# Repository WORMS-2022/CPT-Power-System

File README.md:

# CPT-Power-System
 Power sharing architecture and supporting electronics

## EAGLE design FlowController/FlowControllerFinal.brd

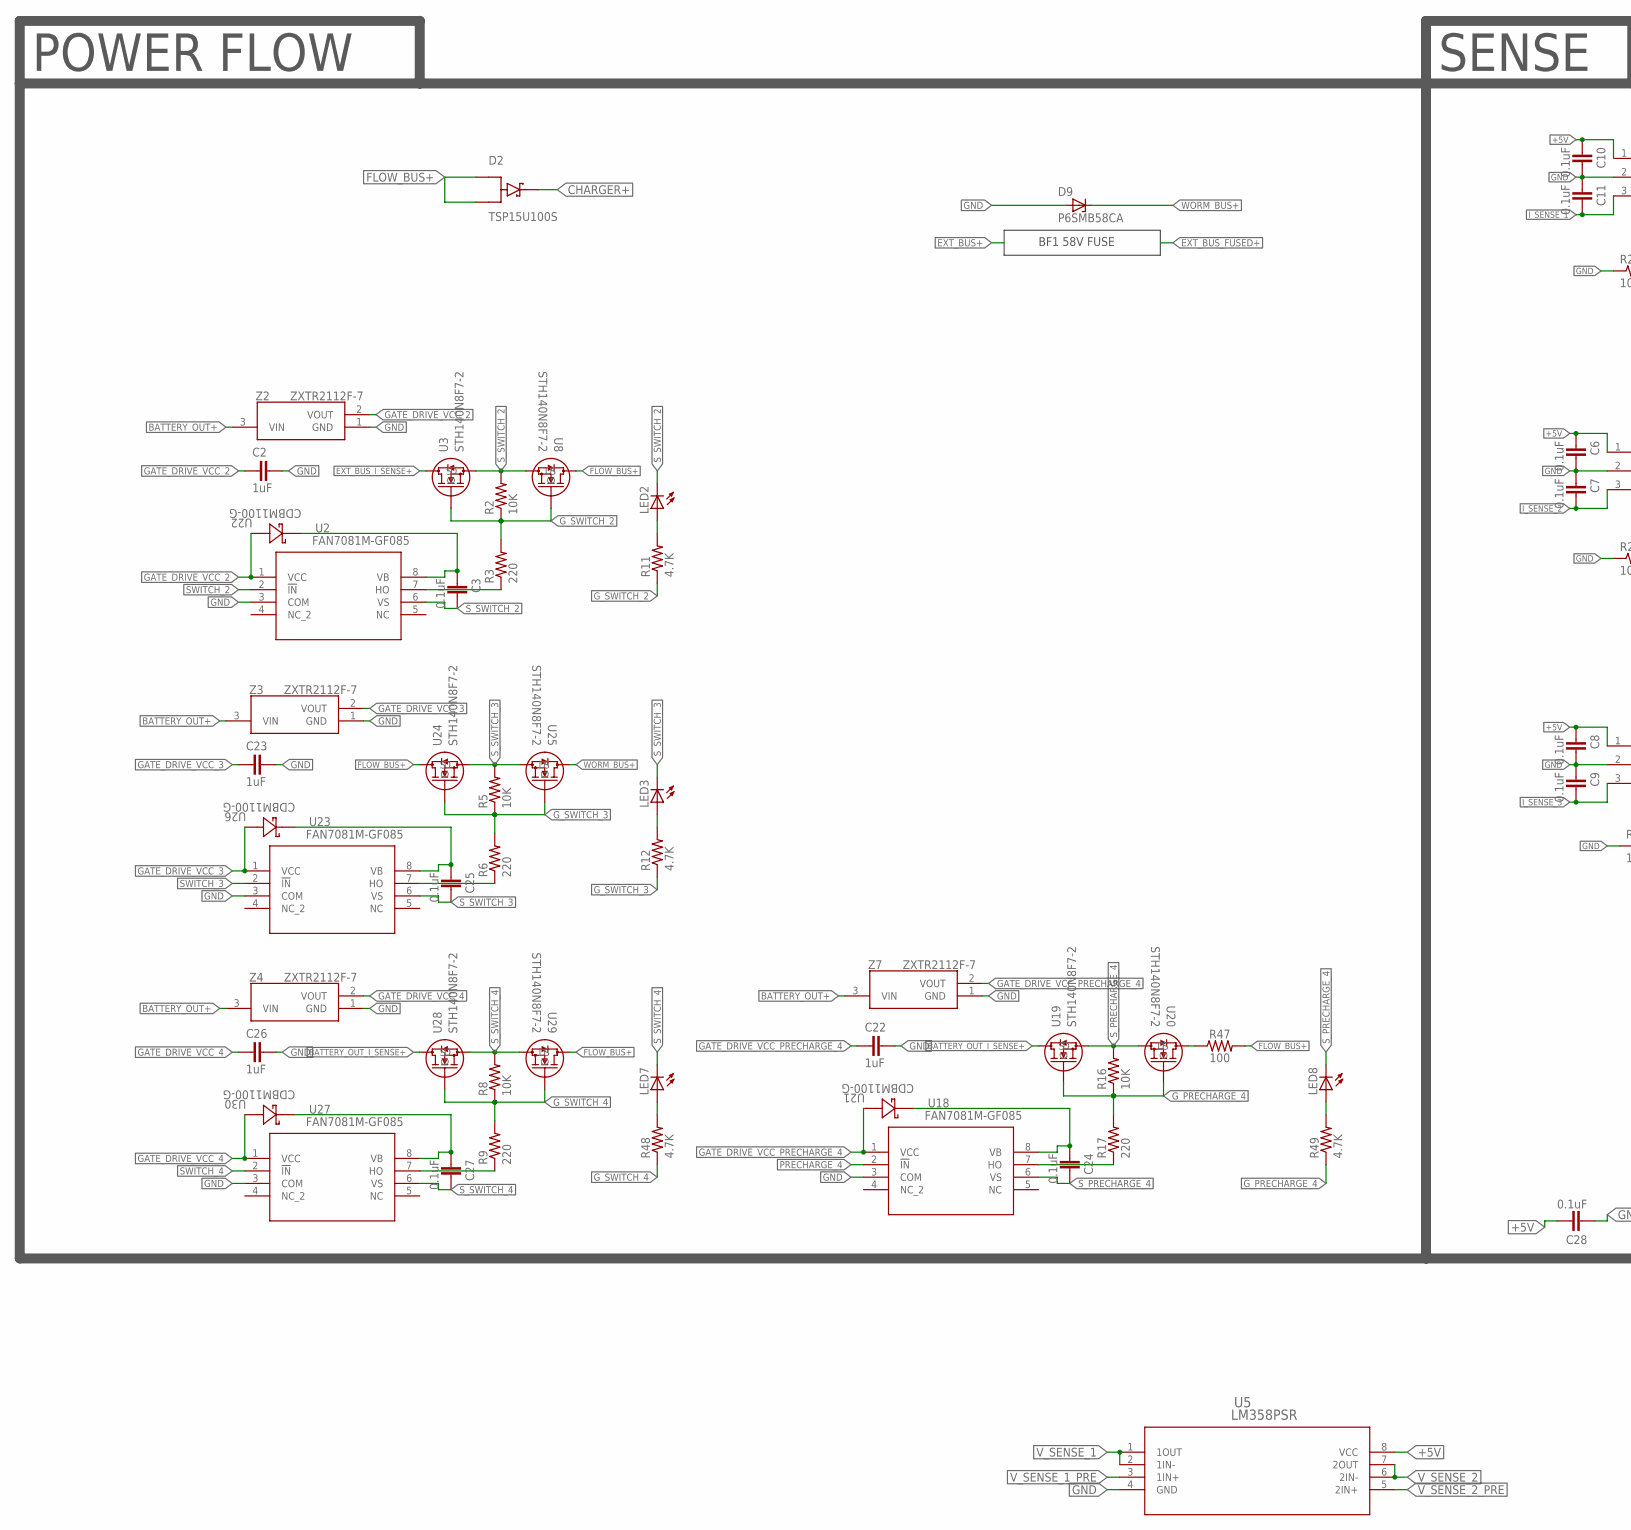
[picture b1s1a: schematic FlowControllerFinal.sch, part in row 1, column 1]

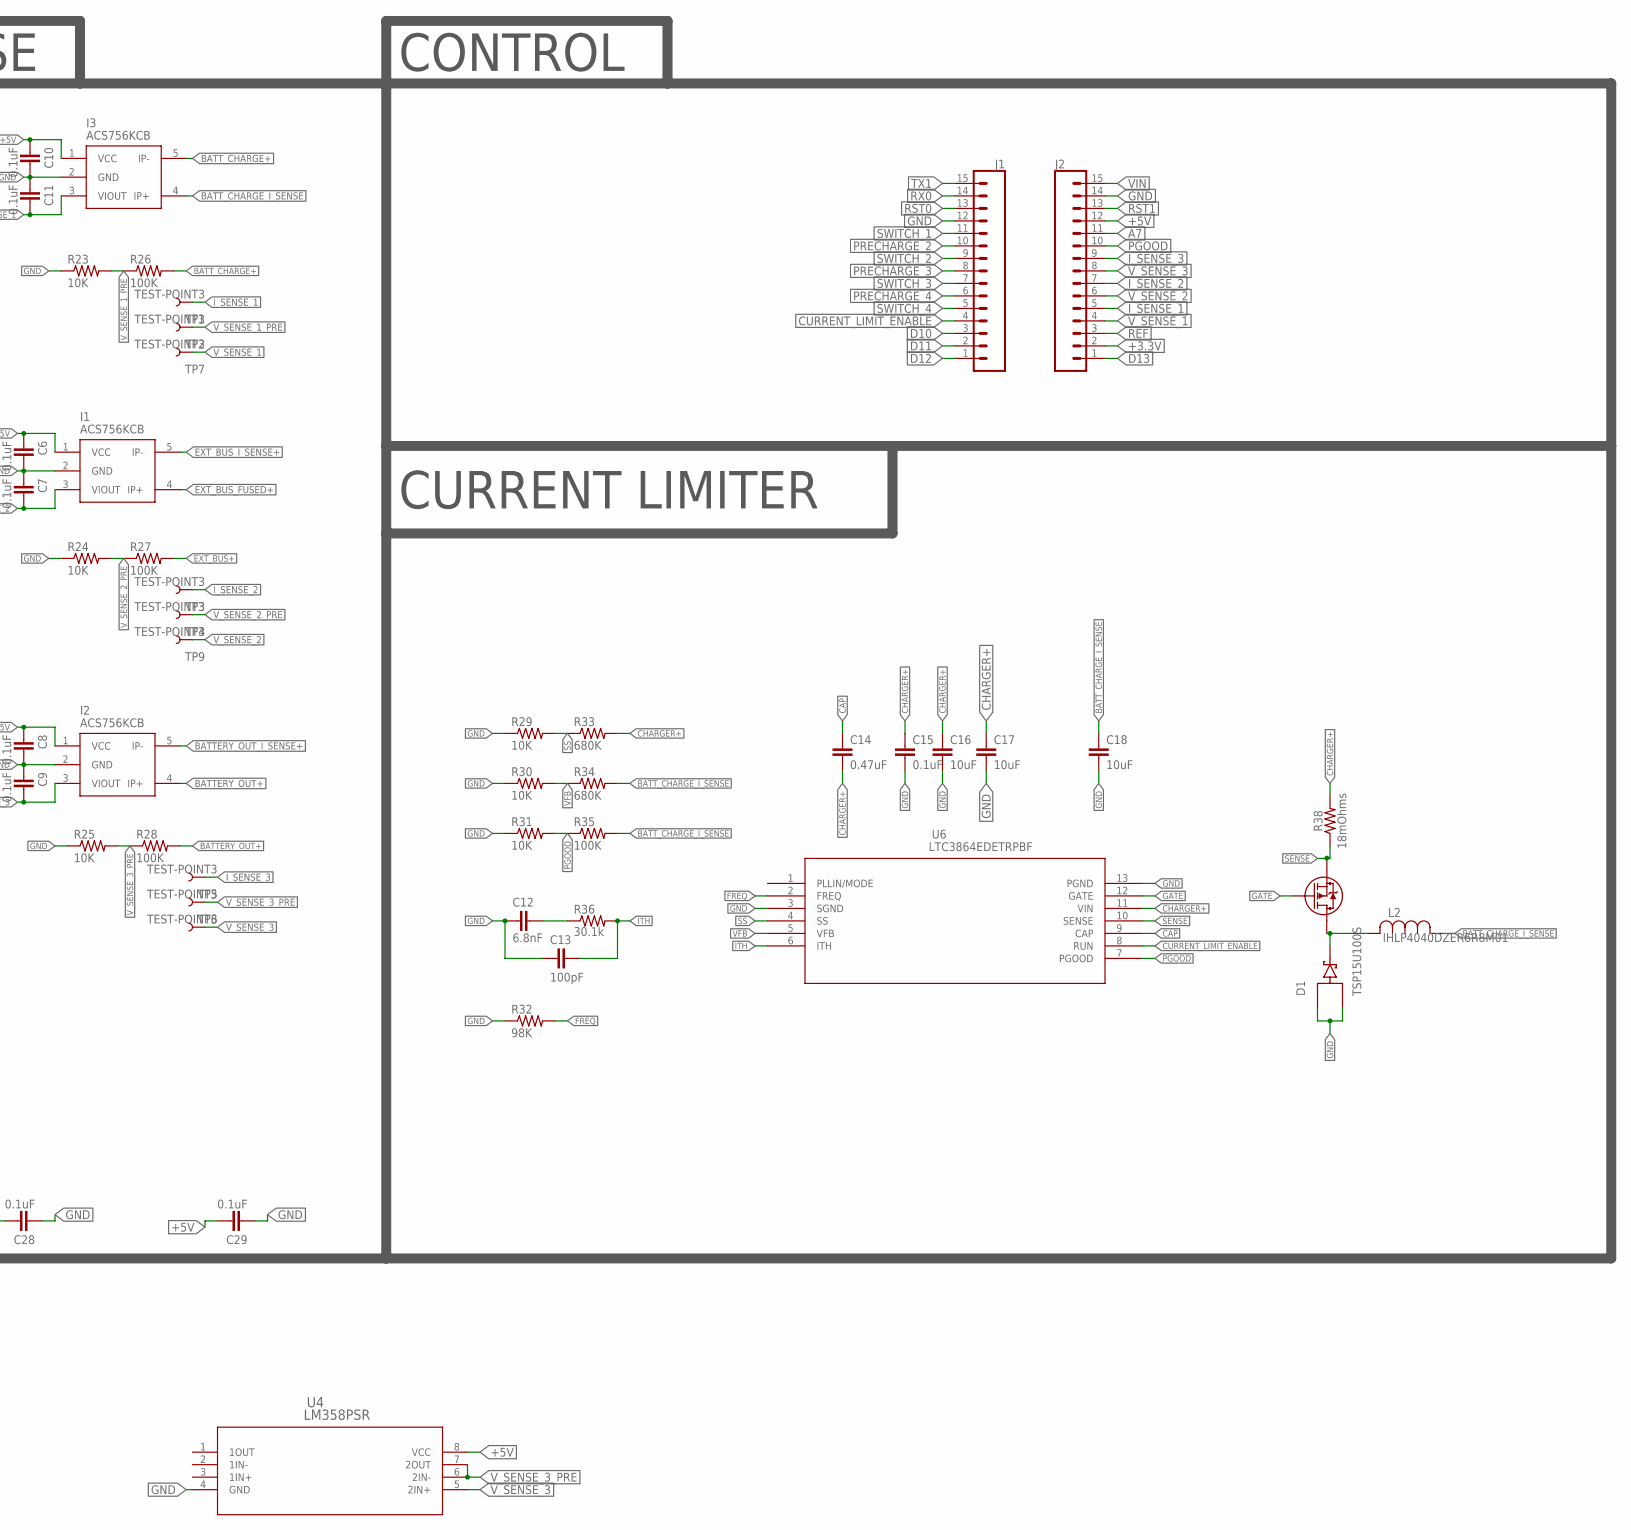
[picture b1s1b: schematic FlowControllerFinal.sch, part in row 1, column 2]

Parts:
C2, C22, C23, C26: 1uF; 0805
C3, C6, C7, C8, C9, C10, C11, C15, C24, C25, C27, C28, C29: 0.1uF; 0805
C12: 6.8nF; 0805
C13: 100pF; 0805
C14: 0.47uF; 0805
C16, C17, C18: 10uF; 1210
D1, D2: TSP15U100S; DIO_TSP15U100S
D9: P6SMB58CA; DO214AA
I1, I2, I3: ACS756KCB
J1, J2: CONN_15; 1X15
L2: IHLP4040DZER6R8M01; IND_IHLP-4040DZ_VIS
LED2, LED3, LED7, LED8: LEDCHIPLED_0805; CHIPLED_0805
R2, R5, R8, R16, R23, R24, R25, R29, R30, R31: 10K; M0805
R3, R6, R9, R17: 220; M0805
R11, R12, R48, R49: 4.7K; M0805
R26, R27, R28, R35: 100K; M0805
R32: 98K; M0805
R33, R34: 680K; M0805
R36: 30.1k; M0805
R37: RSJ250P10TL; TRANS_R5009FNJ_ROM
R38: 18mOhms; 2512
R47: 100; 2512
TP1, TP2, TP3, TP4, TP5, TP6, TP7, TP9, TP11: TEST-POINT3; PAD.03X.03
U2, U18, U23, U27: FAN7081M-GF085; SOIC8_3P9X4P9_ONS
U3, U8, U19, U20, U24, U25, U28, U29: STH140N8F7-2; HPAK_0N8F7-2_STM
U4, U5: LM358PSR; PS8
U6: LTC3864EDETRPBF; DFN-12_DE
U21, U22, U26, U30: CDBM1100-G; CDBM
Z2, Z3, Z4, Z7: ZXTR2112F-7; SOT96P240X110-3N

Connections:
+3.3V: J2.2
+5V: C6.1, C8.1, C10.1, C28.2, C29.2, I1.1 (VCC), I2.1 (VCC), I3.1 (VCC), J2.12, U4.8 (VCC), U5.8 (VCC)
A7: J2.11
BATTERY_OUT+: I2.4 (IP+), R28.2, Z2.3 (VIN), Z3.3 (VIN), Z4.3 (VIN), Z7.3 (VIN)
BATTERY_OUT_I_SENSE+: I2.5 (IP-), U19.2 (D), U28.2 (D)
BATT_CHARGE+: I3.5 (IP-), R26.2
BATT_CHARGE_I_SENSE: C18.1, I3.4 (IP+), L2.1, R34.2, R35.2
CAP: C14.1, U6.9 (CAP)
CHARGER+: C14.2, C15.1, C16.1, C17.1, D2.3 (K), R33.2, R38.P$2 (2), U6.11 (VIN)
CURRENT_LIMIT_ENABLE: J1.4, U6.8 (RUN)
D10: J1.3
D11: J1.2
D12: J1.1
D13: J2.1
EXT_BUS+: R27.2
EXT_BUS_FUSED+: I1.4 (IP+)
EXT_BUS_I_SENSE+: I1.5 (IP-), U3.2 (D)
FLOW_BUS+: D2.1 (A1), D2.2 (A2), R47.P$2 (2), U8.2 (D), U24.2 (D), U29.2 (D)
FREQ: R32.2, U6.2 (FREQ)
GATE: R37.1, U6.12 (GATE)
GATE_DRIVE_VCC_2: C2.1, U2.1 (VCC), U22.2, Z2.2 (VOUT)
GATE_DRIVE_VCC_3: C23.1, U23.1 (VCC), U26.2, Z3.2 (VOUT)
GATE_DRIVE_VCC_4: C26.1, U27.1 (VCC), U30.2, Z4.2 (VOUT)
GATE_DRIVE_VCC_PRECHARGE_4: C22.1, U18.1 (VCC), U21.2, Z7.2 (VOUT)
GND: C2.2, C6.2, C7.1, C8.2, C9.1, C10.2, C11.1, C12.1, C13.1, C15.2, C16.2, C17.2, C18.2, C22.2, C23.2, C26.2, C28.1, C29.1, D1.1 (A1), D1.2 (A2), D9.A, I1.2 (GND), I2.2 (GND), I3.2 (GND), J1.12, J2.14, R23.1, R24.1, R25.1, R29.1, R30.1, R31.1, R32.1, U2.3 (COM), U4.4 (GND), U5.4 (GND), U6.3 (SGND), U6.13 (PGND), U18.3 (COM), U23.3 (COM), U27.3 (COM), Z2.1 (GND), Z3.1 (GND), Z4.1 (GND), Z7.1 (GND)
G_PRECHARGE_4: R16.1, R17.2, R49.1, U19.1 (G), U20.1 (G)
G_SWITCH_2: R2.1, R3.2, R11.1, U3.1 (G), U8.1 (G)
G_SWITCH_3: R5.1, R6.2, R12.1, U24.1 (G), U25.1 (G)
G_SWITCH_4: R8.1, R9.2, R48.1, U28.1 (G), U29.1 (G)
ITH: C13.2, R36.2, U6.6 (ITH)
I_SENSE_1: C11.2, I3.3 (VIOUT), J2.5, TP1.P$1
I_SENSE_2: C7.2, I1.3 (VIOUT), J2.7, TP3.P$1
I_SENSE_3: C9.2, I2.3 (VIOUT), J2.9, TP5.P$1
unnamed: LED8.A, R49.2
unnamed: LED2.A, R11.2
unnamed: R3.1, U2.7 (HO)
unnamed: C3.1, U2.8 (VB), U22.1
unnamed: R47.P$1 (1), U20.2 (D)
unnamed: R6.1, U23.7 (HO)
unnamed: C25.1, U23.8 (VB), U26.1
unnamed: R17.1, U18.7 (HO)
unnamed: R9.1, U27.7 (HO)
unnamed: C24.1, U18.8 (VB), U21.1
unnamed: C27.1, U27.8 (VB), U30.1
unnamed: C12.2, R36.1
unnamed: D1.3 (K), L2.2, R37.2 (3)
unnamed: LED3.A, R12.2
unnamed: LED7.A, R48.2
PGOOD: J2.10, R31.2, R35.1, U6.7 (PGOOD)
PRECHARGE_2: J1.10
PRECHARGE_3: J1.8
PRECHARGE_4: J1.6, U18.2 (!IN)
REF: J2.3
RST0: J1.13
RST1: J2.13
RX0: J1.14
SENSE: R37.3 (2), R38.P$1 (1), U6.10 (SENSE)
SS: R29.2, R33.1, U6.4 (SS)
SWITCH_1: J1.11
SWITCH_2: J1.9, U2.2 (!IN)
SWITCH_3: J1.7, U23.2 (!IN)
SWITCH_4: J1.5, U27.2 (!IN)
S_PRECHARGE_4: C24.2, LED8.C, R16.2, U18.6 (VS), U19.3 (S), U20.3 (S)
S_SWITCH_2: C3.2, LED2.C, R2.2, U2.6 (VS), U3.3 (S), U8.3 (S)
S_SWITCH_3: C25.2, LED3.C, R5.2, U23.6 (VS), U24.3 (S), U25.3 (S)
S_SWITCH_4: C27.2, LED7.C, R8.2, U27.6 (VS), U28.3 (S), U29.3 (S)
TX1: J1.15
VFB: R30.2, R34.1, U6.5 (VFB)
VIN: J2.15
V_SENSE_1: J2.4, TP7.P$1, U5.1 (1OUT), U5.2 (1IN-)
V_SENSE_1_PRE: R23.2, R26.1, TP2.P$1, U5.3 (1IN+)
V_SENSE_2: J2.6, TP9.P$1, U5.6 (2IN-), U5.7 (2OUT)
V_SENSE_2_PRE: R24.2, R27.1, TP4.P$1, U5.5 (2IN+)
V_SENSE_3: J2.8, TP11.P$1, U4.5 (2IN+)
V_SENSE_3_PRE: R25.2, R28.1, TP6.P$1, U4.6 (2IN-), U4.7 (2OUT)
WORM_BUS+: D9.C, U25.2 (D)

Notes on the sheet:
POWER FLOW
SENSE
CONTROL
CURRENT LIMITER
BF1 58V FUSE

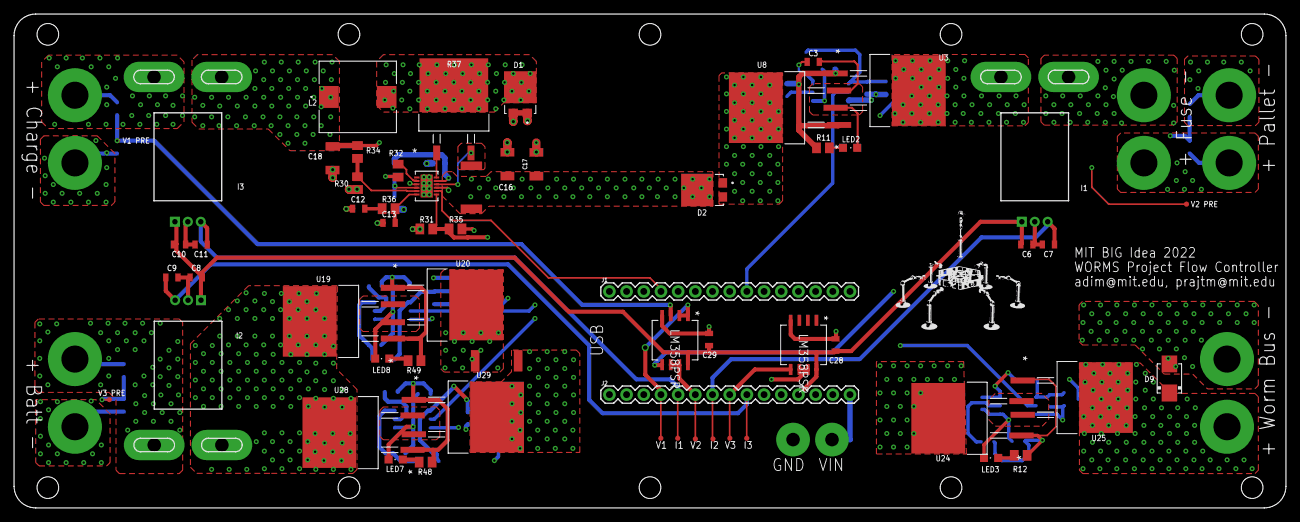
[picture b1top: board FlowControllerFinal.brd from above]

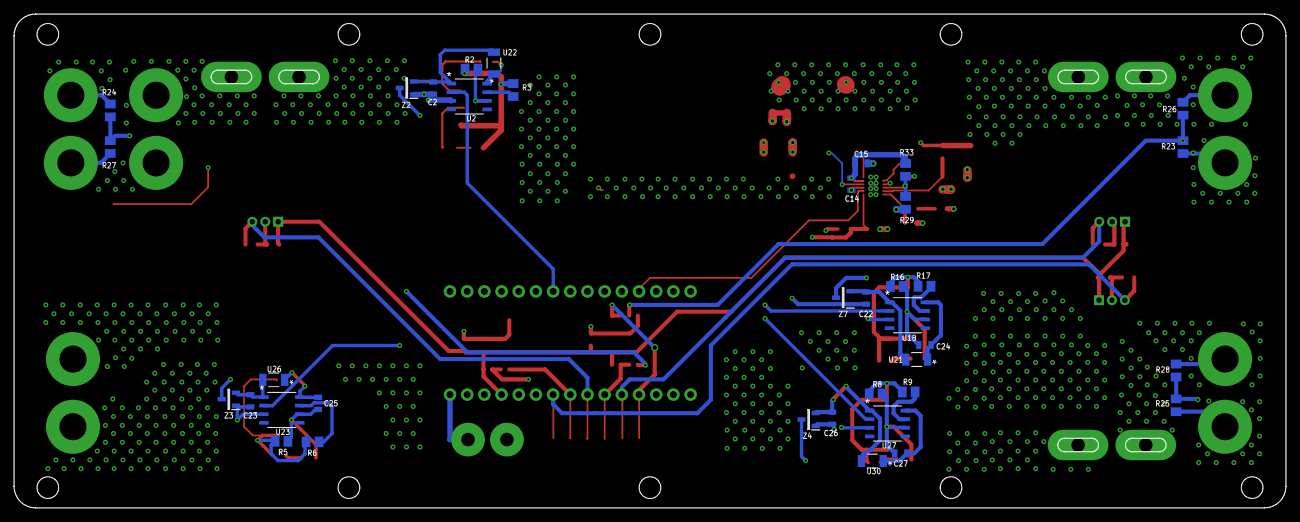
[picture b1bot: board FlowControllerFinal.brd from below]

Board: 4 copper layers, 188.0 x 73.0 mm, 97 parts (37 on the bottom side), 59 nets.

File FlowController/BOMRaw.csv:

"Qty";"Value";"Device";"Package";"Parts";"Description";"COPYRIGHT";"DESCRIPTION";"DIGI-KEY_PART_NUMBER";"DIGI-KEY_PART_NUMBER_1";"DIGI-KEY_PART_NUMBER_2";"DIGI-KEY_PART_NUMBER_3";"DIGI-KEY_PART_NUMBER_4";"HEIGHT";"MANUFACTURER_NAME";"MANUFACTURER_PART_NUMBER";"MF";"MFR_NAME";"MOUSER_PART_NUMBER";"MOUSER_PRICE-STOCK";"MP";"MPN";"OC_FARNELL";"OC_NEWARK";"PACKAGE";"PROD_ID";"PURCHASE-URL";"SPICEPREFIX";"VALUE";
"1";"";"CONN_15";"1X15";"J1";"Multi connection point. Often used as Generic Header-pin footprint for 0.1 inch spaced/style header connections";"";"";"";"";"";"";"";"";"";"";"";"";"";"";"";"";"";"";"";"";"";"";"";
"1";"";"CONN_15";"1X15";"J2";"Multi connection point. Often used as Generic Header-pin footprint for 0.1 inch spaced/style header connections";"";"";"";"";"";"";"";"";"";"";"";"";"";"";"";"";"";"";"";"";"";"X";"";
"4";"";"LEDCHIPLED_0805";"CHIPLED_0805";"LED2, LED3, LED7, LED8";"LED";"";"";"";"";"";"";"";"";"";"";"";"";"";"";"";"";"";"";"";"";"";"";"";
"13";"0.1uF";"2.2UF-0805-25V-(+80/-20%)";"0805";"C3, C6, C7, C8, C9, C10, C11, C15, C24, C25, C27, C28, C29";"2.2µF ceramic capacitors";"";"";"";"";"";"";"";"";"";"";"";"";"";"";"";"";"";"";"";"CAP-11624";"";"";"2.2uF";
"1";"0.47uF";"2.2UF-0805-25V-(+80/-20%)";"0805";"C14";"2.2µF ceramic capacitors";"";"";"";"";"";"";"";"";"";"";"";"";"";"";"";"";"";"";"";"CAP-11624";"";"";"2.2uF";
"1";"100";"0.05OHM-2512-3W-1%";"2512";"R47";"0.05Ω resistor";"";"";"";"";"";"";"";"";"";"";"";"";"";"";"";"";"";"";"";"RES-13771";"";"";"0.05";
"4";"100K";"R-US_M0805";"M0805";"R26, R27, R28, R35";"RESISTOR, American symbol";"";"";"";"";"";"";"";"";"";"";"";"";"";"";"";"";"";"";"";"";"";"";"";
"1";"100pF";"2.2UF-0805-25V-(+80/-20%)";"0805";"C13";"2.2µF ceramic capacitors";"";"";"";"";"";"";"";"";"";"";"";"";"";"";"";"";"";"";"";"CAP-11624";"";"";"2.2uF";
"10";"10K";"R-US_M0805";"M0805";"R2, R5, R8, R16, R23, R24, R25, R29, R30, R31";"RESISTOR, American symbol";"";"";"";"";"";"";"";"";"";"";"";"";"";"";"";"";"";"";"";"";"";"";"";
"3";"10uF";"10UF-1210-50V-20%";"1210";"C16, C17, C18";"10.0µF ceramic capacitors";"";"";"";"";"";"";"";"";"";"";"";"";"";"";"";"";"";"";"";"CAP-09824";"";"";"10uF";
"1";"18mOhms";"0.05OHM-2512-3W-1%";"2512";"R38";"0.05Ω resistor";"";"";"";"";"";"";"";"";"";"";"";"";"";"";"";"";"";"";"";"RES-13771";"";"";"0.05";
"4";"1uF";"2.2UF-0805-25V-(+80/-20%)";"0805";"C2, C22, C23, C26";"2.2µF ceramic capacitors";"";"";"";"";"";"";"";"";"";"";"";"";"";"";"";"";"";"";"";"CAP-11624";"";"";"2.2uF";
"4";"220";"R-US_M0805";"M0805";"R3, R6, R9, R17";"RESISTOR, American symbol";"";"";"";"";"";"";"";"";"";"";"";"";"";"";"";"";"";"";"";"";"";"";"";
"1";"30.1k";"R-US_M0805";"M0805";"R36";"RESISTOR, American symbol";"";"";"";"";"";"";"";"";"";"";"";"";"";"";"";"";"";"";"";"";"";"";"";
"4";"4.7K";"R-US_M0805";"M0805";"R11, R12, R48, R49";"RESISTOR, American symbol";"";"";"";"";"";"";"";"";"";"";"";"";"";"";"";"";"";"";"";"";"";"";"";
"1";"6.8nF";"2.2UF-0805-25V-(+80/-20%)";"0805";"C12";"2.2µF ceramic capacitors";"";"";"";"";"";"";"";"";"";"";"";"";"";"";"";"";"";"";"";"CAP-11624";"";"";"2.2uF";
"2";"680K";"R-US_M0805";"M0805";"R33, R34";"RESISTOR, American symbol";"";"";"";"";"";"";"";"";"";"";"";"";"";"";"";"";"";"";"";"";"";"";"";
"1";"98K";"R-US_M0805";"M0805";"R32";"RESISTOR, American symbol";"";"";"";"";"";"";"";"";"";"";"";"";"";"";"";"";"";"";"";"";"";"";"";
"3";"ACS756KCB";"ACS756KCB";"ACS756KCB";"I1, I2, I3";"";"";"";"";"";"";"";"";"";"";"";"";"";"";"";"";"";"";"";"";"";"";"";"";
"4";"CDBM1100-G";"CDBM1100-G";"CDBM";"U21, U22, U26, U30";"";"Copyright (C) 2022 Ultra Librarian. All rights reserved.";"";"";"641-1331-1-ND";"641-1331-2-ND";"641-1331-2-NDL";"641-1331-6-ND";"";"";"CDBM1100-G";"";"Comchip";"";"";"";"";"";"";"";"";"";"";"";
"4";"FAN7081M-GF085";"FAN7081M-GF085";"SOIC8_3P9X4P9_ONS";"U2, U18, U23, U27";"";"Copyright (C) 2022 Ultra Librarian. All rights reserved.";"";"";"FAN7081M-GF085-ND";"";"";"";"";"";"FAN7081M-GF085";"";"onsemi";"";"";"";"";"";"";"";"";"";"";"";
"1";"IHLP4040DZER6R8M01";"IHLP4040DZER6R8M01";"IND_IHLP-4040DZ_VIS";"L2";"";"Copyright (C) 2022 Ultra Librarian. All rights reserved.";"";"";"541-1303-1-ND";"541-1303-2-ND";"541-1303-6-ND";"";"";"";"IHLP4040DZER6R8M01";"";"Vishay";"";"";"";"";"";"";"";"";"";"";"";
"2";"LM358PSR";"LM358PSR";"PS8";"U4, U5";"";"Copyright (C) 2022 Ultra Librarian. All rights reserved.";"";"";"296-1396-1-ND";"296-1396-2-ND";"296-1396-6-ND";"2156-LM358PSR-ND";"";"";"LM358PSR";"";"Texas Instruments";"";"";"";"";"";"";"";"";"";"";"";
"1";"LTC3864EDETRPBF";"LTC3864EDETRPBF";"DFN-12_DE";"U6";"";"";" Buck Regulator Positive Output Step-Down - DC-DC Controller IC 12-DFN (4x3) ";"161-LTC3864EDE#TRPBFTR-ND";"";"";"";"";"";"";"";"Analog Devices";"";"";"";"LTC3864EDE#TRPBF";"";"";"";"DFN -12 Analog Devices";"";"https://pricing.snapeda.com/search/part/LTC3864EDE#TRPBF/?ref=eda";"";"";
"1";"P6SMB58CA";"1SMB5913BT3G";"DO214AA";"D9";"1SMB59xxBT3G Series";"";"";"";"";"";"";"";"";"";"";"ON Semiconductor";"";"";"";"";"1SMB5913BT3G";"1431155";"88H5165";"";"";"";"";"";
"1";"RSJ250P10TL";"RSJ250P10TL";"TRANS_R5009FNJ_ROM";"R37";"";"Copyright (C) 2022 Ultra Librarian. All rights reserved.";"";"";"RSJ250P10TLCT-ND";"RSJ250P10TLDKR-ND";"RSJ250P10TLTR-ND";"";"";"";"RSJ250P10TL";"";"ROHM Semiconductor";"";"";"";"";"";"";"";"";"";"";"";
"8";"STH140N8F7-2";"STH140N8F7-2";"HPAK_0N8F7-2_STM";"U3, U8, U19, U20, U24, U25, U28, U29";"";"Copyright (C) 2022 Ultra Librarian. All rights reserved.";"";"";"497-14534-2-ND";"497-14534-1-ND";"497-14534-6-ND";"";"";"";"STH140N8F7-2";"";"STMicroelectronics";"";"";"";"";"";"";"";"";"";"";"";
"9";"TEST-POINT3";"TEST-POINT3";"PAD.03X.03";"TP1, TP2, TP3, TP4, TP5, TP6, TP7, TP9, TP11";"SparkFun Test Points";"";"";"";"";"";"";"";"";"";"";"";"";"";"";"";"";"";"";"";"";"";"";"";
"2";"TSP15U100S";"TSP15U100S";"DIO_TSP15U100S";"D1, D2";"";"";" 15A, 100V, Trench Schottky ";"1801-TSP15U100STR-ND";"";"";"";"";"";"";"";"Taiwan Semiconductor";"";"";"";"TSP15U100S";"";"";"";"SMPC Taiwan Semiconductor";"";"https://pricing.snapeda.com/search/part/TSP15U100S/?ref=eda";"";"";
"4";"ZXTR2112F-7";"ZXTR2112F-7";"SOT96P240X110-3N";"Z2, Z3, Z4, Z7";"Linear Voltage Regulators Transistor Array Zener Linear Reg";"";"Linear Voltage Regulators Transistor Array Zener Linear Reg";"";"";"";"";"";"1.1mm";"Diodes Inc.";"ZXTR2112F-7";"";"";"621-ZXTR2112F-7";"https://www.mouser.co.uk/ProductDetail/Diodes-Incorporated/Z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";"";"";"";"";"";"";"";"";"";

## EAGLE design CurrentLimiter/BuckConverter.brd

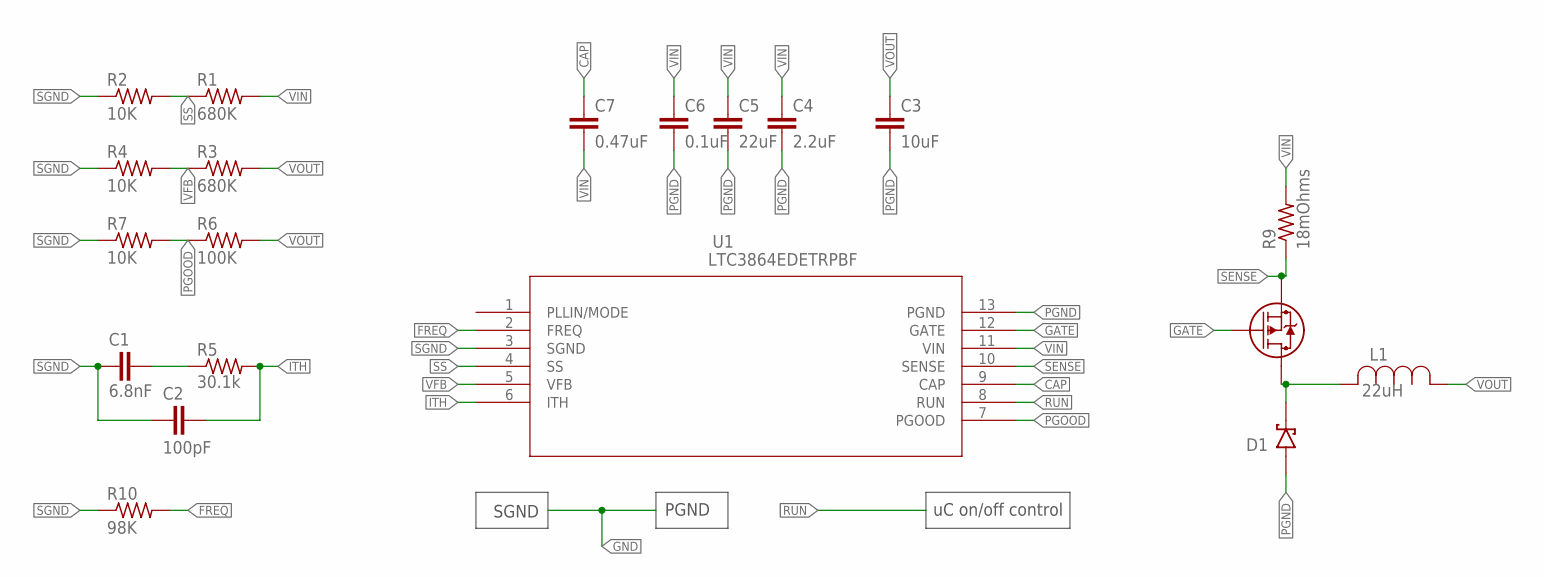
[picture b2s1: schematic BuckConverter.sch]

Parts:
C1: 6.8nF; 0805
C2: 100pF; 0805
C3: 10uF; 0805
C4: 2.2uF; 0805
C5: 22uF; 0805
C6: 0.1uF; 0805
C7: 0.47uF; 0805
D1: MBR1560STR; DIO_MBR1560STR
L1: 22uH; IND_IHLP-4040DZ_VIS
R1, R3: 680K; M0805
R2, R4, R7: 10K; M0805
R5: 30.1k; M0805
R6: 100K; M0805
R8: RSJ250P10TL; TRANS_R5009FNJ_ROM
R9: 18mOhms; M0805
R10: 98K; M0805
U1: LTC3864EDETRPBF; DFN-12_DE

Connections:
CAP: C7.1, U1.9 (CAP)
FREQ: R10.2, U1.2 (FREQ)
GATE: R8.1, U1.12 (GATE)
ITH: C2.2, R5.2, U1.6 (ITH)
unnamed: D1.3 (K), D1.4 (K), L1.2, R8.2 (3)
unnamed: C1.2, R5.1
PGND: C3.2, C4.2, C5.2, C6.2, D1.1 (A), D1.2 (A), U1.13 (PGND)
PGOOD: R6.1, R7.2, U1.7 (PGOOD)
RUN: U1.8 (RUN)
SENSE: R8.3 (2), R9.1, U1.10 (SENSE)
SGND: C1.1, C2.1, R2.1, R4.1, R7.1, R10.1, U1.3 (SGND)
SS: R1.1, R2.2, U1.4 (SS)
VFB: R3.1, R4.2, U1.5 (VFB)
VIN: C4.1, C5.1, C6.1, C7.2, R1.2, R9.2, U1.11 (VIN)
VOUT: C3.1, L1.1, R3.2, R6.2

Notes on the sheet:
uC on/off control
PGND
SGND

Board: 2 copper layers, 20 parts (0 on the bottom side), 14 nets, no tracks yet.

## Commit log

2022-05-15 buck current limiter file upload
2022-05-17 Flow controller schematic
2022-05-23 schematic draft 2
2022-05-24 n channel variation
2022-05-24 datasheets
2022-06-05 Finished PCB upload
2022-06-11 Finalized board and CAM files

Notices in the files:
parts and their libraries:
SparkFun-Capacitors: Licensing: Creative Commons ShareAlike 4.0 International - https://creativecommons.org/licenses/by-sa/4.0
COPYRIGHT: Copyright (C) 2022 Ultra Librarian. All rights reserved.
